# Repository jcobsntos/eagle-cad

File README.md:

# 🦅 EAGLE CAD Projects 

## 🎯 Overview

This repository contains EAGLE CAD design files for various electronics projects, including:

🎨 Footprints, Packages, Devices, and Symbols for PCB design

🛠️ Laboratories covering schematic and board designs

⚡ Multilevel Power Supply Project with a complete schematic and PCB layout

## 🤝 Contributing

Contributions are welcome! 🛠️ Feel free to submit pull requests for improvements, additional laboratories, or new PCB designs.

## Authors

- [@jcobsntos](https://github.com/jcobsntos)

## 🔗 Links

## 🏆 Tools

PCB design software for everyone 🖥️ https://www.autodesk.com/products/eagle/free-download

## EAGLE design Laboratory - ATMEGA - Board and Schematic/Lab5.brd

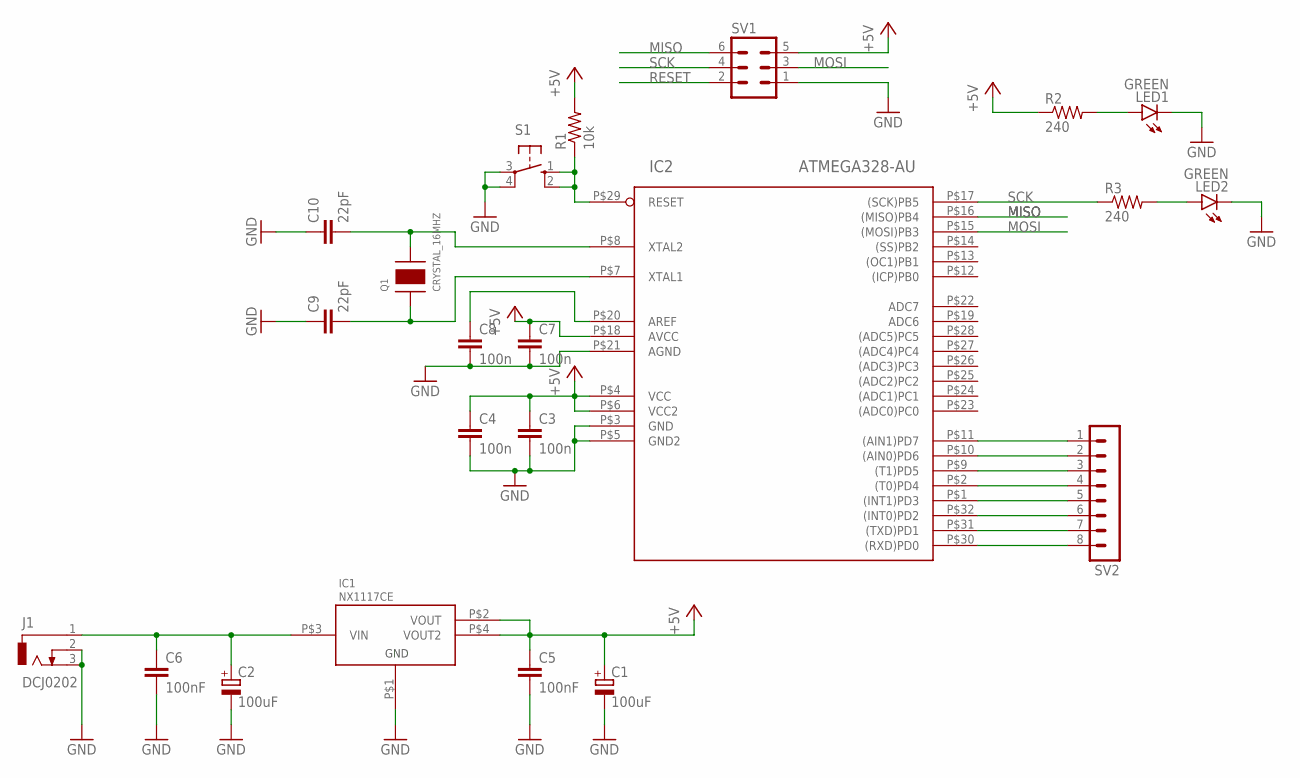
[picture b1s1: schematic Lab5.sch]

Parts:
C1, C2: 100uF; PANASONIC_D
C3, C4, C7, C8: 100n; C0603
C5, C6: 100nF; C0805
C9, C10: 22pF; C0603
IC1: NX1117CE; SOT223_NX
IC2: ATMEGA328-AU; 32-TQFP
J1: DCJ0202
LED1, LED2: GREEN; CHIP-LED0603
Q1: CRYSTAL_16MHZ
R1: 10k; R0603
R2, R3: 240; R0603
S1: 10-XX; B3F-10XX
SV1: MA03-2
SV2: MA08-1

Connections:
+5V: C1.+, C3.1, C4.1, C5.1, C7.1, IC1.P$2 (VOUT), IC1.P$4 (VOUT2), IC2.P$4 (VCC), IC2.P$6 (VCC2), IC2.P$18 (AVCC), R1.2, R2.1, SV1.5
GND: C1.-, C2.-, C3.2, C4.2, C5.2, C6.2, C7.2, C8.2, C9.1, C10.1, IC1.P$1 (GND), IC2.P$3 (GND), IC2.P$5 (GND2), IC2.P$21 (AGND), J1.2, J1.3, LED1.C, LED2.C, S1.3, S1.4 (P1), SV1.1
MISO: IC2.P$16 ((MISO)PB4), SV1.6
MOSI: IC2.P$15 ((MOSI)PB3), SV1.3
unnamed: C2.+, C6.1, IC1.P$3 (VIN), J1.1
unnamed: C8.1, IC2.P$20 (AREF)
unnamed: C9.2, IC2.P$7 (XTAL1), Q1.P$1
unnamed: C10.2, IC2.P$8 (XTAL2), Q1.P$2
unnamed: IC2.P$29 (RESET), R1.1, S1.1 (S), S1.2 (S1)
unnamed: LED1.A, R2.2
unnamed: LED2.A, R3.2
unnamed: IC2.P$11 ((AIN1)PD7), SV2.1
unnamed: IC2.P$10 ((AIN0)PD6), SV2.2
unnamed: IC2.P$9 ((T1)PD5), SV2.3
unnamed: IC2.P$2 ((T0)PD4), SV2.4
unnamed: IC2.P$1 ((INT1)PD3), SV2.5
unnamed: IC2.P$32 ((INT0)PD2), SV2.6
unnamed: IC2.P$31 ((TXD)PD1), SV2.7
unnamed: IC2.P$30 ((RXD)PD0), SV2.8
RESET: SV1.2
SCK: IC2.P$17 ((SCK)PB5), R3.1, SV1.4

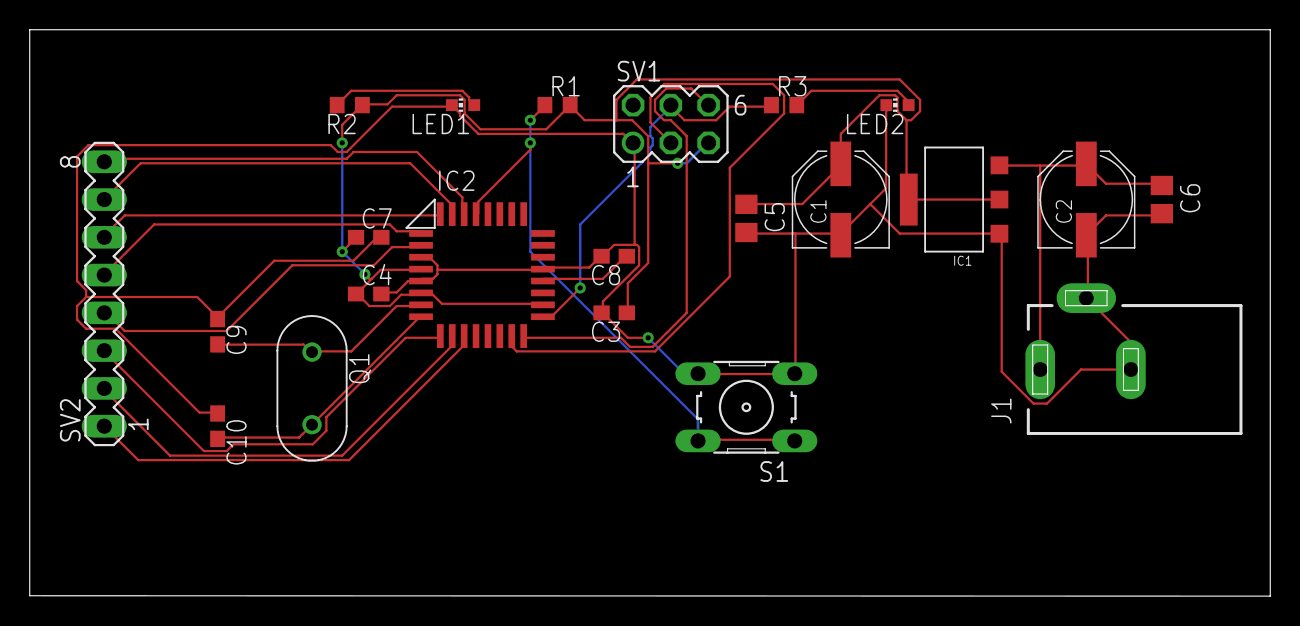
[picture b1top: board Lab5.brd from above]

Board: 2 copper layers, 83.4 x 38.1 mm, 22 parts (0 on the bottom side), 20 nets.

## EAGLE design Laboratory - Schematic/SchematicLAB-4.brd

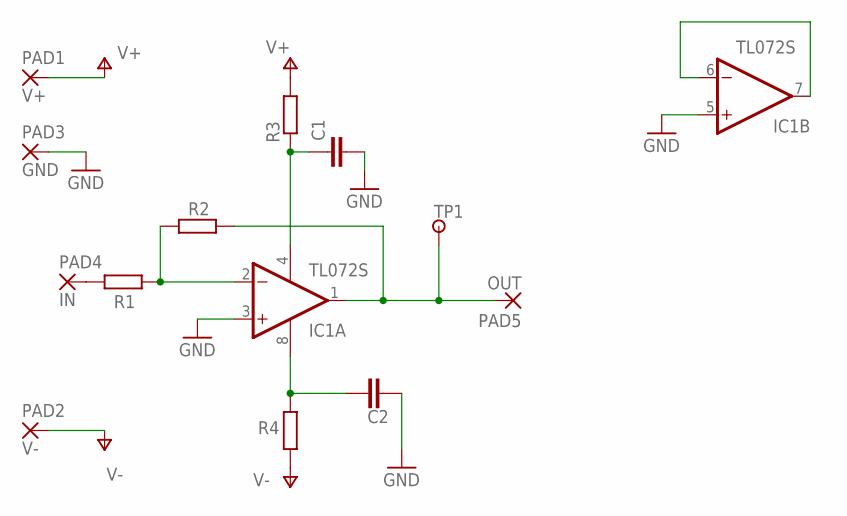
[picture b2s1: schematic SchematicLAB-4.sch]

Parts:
C1, C2: C2.5P; C025-030X050
IC1: TL072S; SOCKED-08
PAD1: V+; 2,54/1,1
PAD2: V-; 2,54/1,1
PAD3: GND; 2,54/1,1
PAD4: IN; 2,54/1,1
PAD5: OUT; 2,54/1,1
R1, R2, R3, R4: R; 0207/10
TP1: PAD-TESTPOINT; 1,6/0,8

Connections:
GND: C1.2, C2.1, IC1.3 (+IN), IC1.5 (+IN), PAD3.1
unnamed: PAD4.1, R1.1
unnamed: IC1.2 (-IN), R1.2, R2.1
unnamed: C1.1, IC1.4 (V-), R3.1
unnamed: IC1.1 (OUT), PAD5.1, R2.2, TP1.1
unnamed: C2.2, IC1.8 (V+), R4.2
unnamed: IC1.6 (-IN), IC1.7 (OUT)
V+: PAD1.1, R3.2
V-: PAD2.1, R4.1

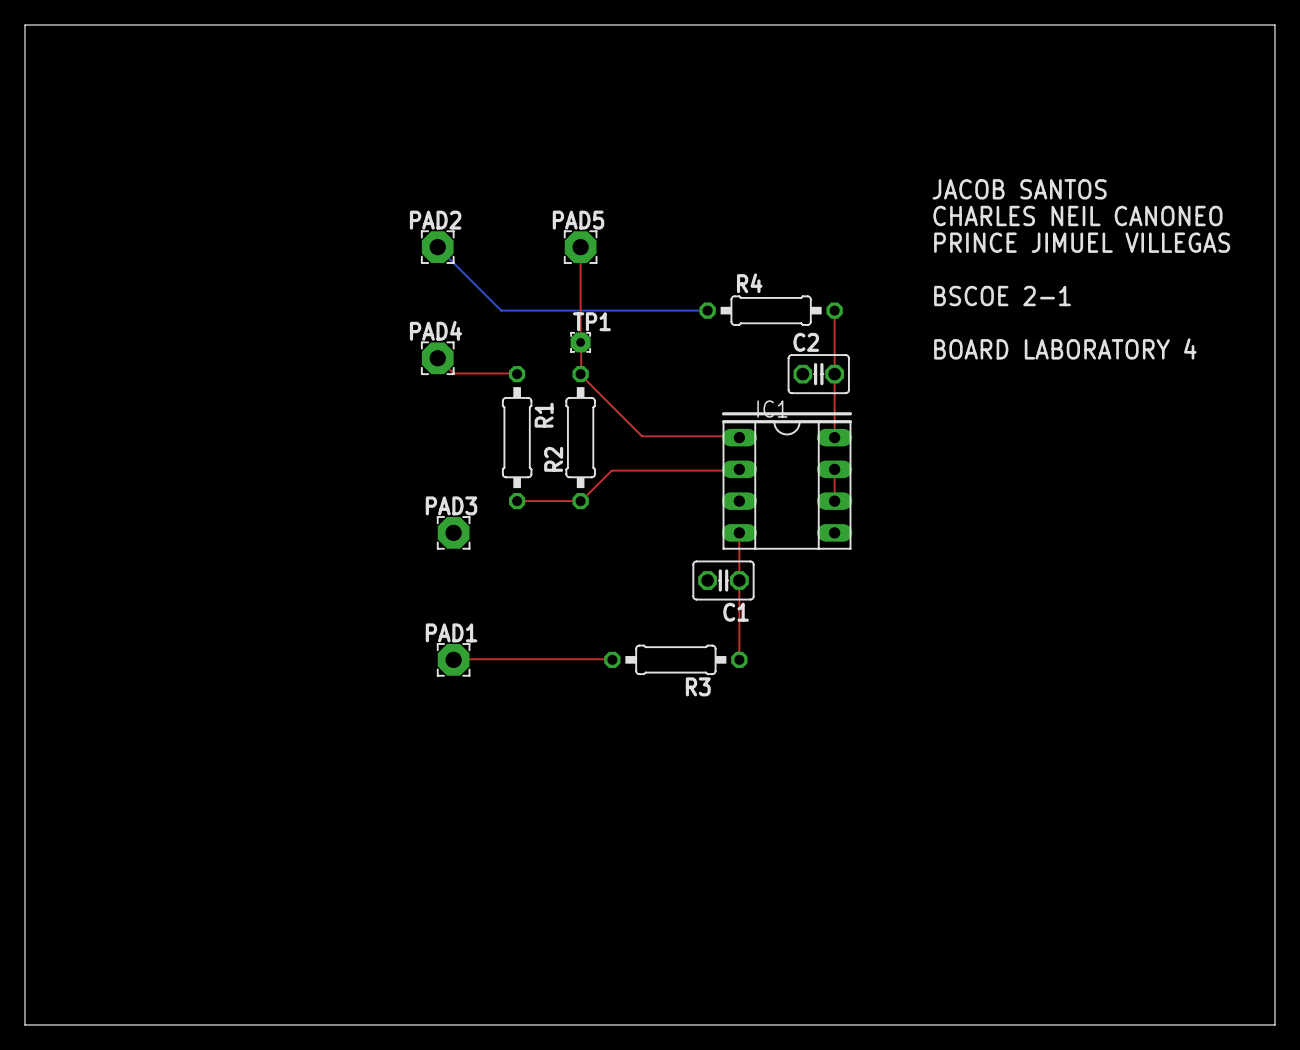
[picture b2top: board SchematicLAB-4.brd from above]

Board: 2 copper layers, 100.0 x 80.0 mm, 13 parts (0 on the bottom side), 9 nets.

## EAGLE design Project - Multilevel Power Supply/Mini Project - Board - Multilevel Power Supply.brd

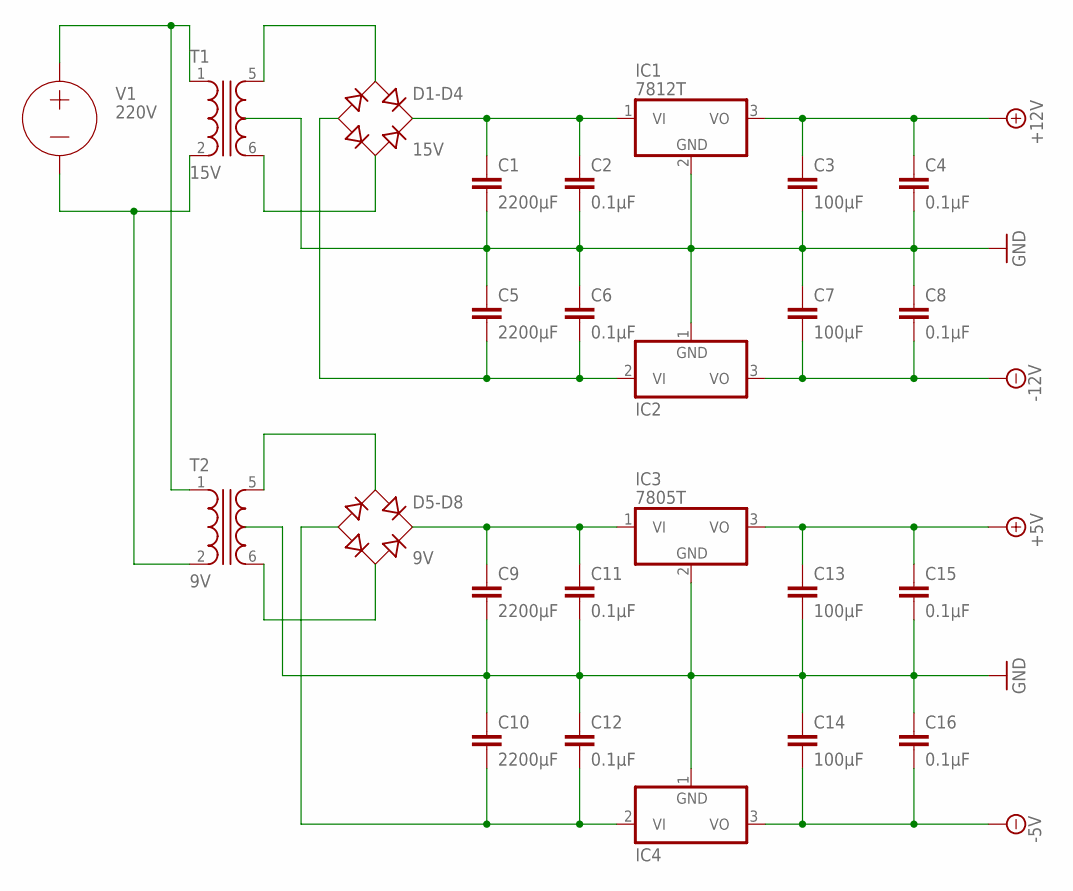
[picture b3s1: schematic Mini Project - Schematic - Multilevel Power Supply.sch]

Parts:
C1, C5, C9, C10: 2200μF; C025-024X044
C2, C4, C6, C8, C11, C12, C15, C16: 0.1μF; C025-024X044
C3, C7, C13, C14: 100μF; C025-024X044
D1-D4: 15V; SOIC-4
D5-D8: 9V; SOIC-4
IC1: 7812T; TO220H
IC2: 7912T; TO220H
IC3: 7805T; TO220H
IC4: 7905T; TO220H
T1: 15V; T70-E
T2: 9V; T70-E

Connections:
+5V: C13.1, C15.1, IC3.3 (VO)
+12V: C3.1, C4.1, IC1.3 (VO)
-5V: C14.2, C16.2, IC4.3 (VO)
-12V: C7.2, C8.2, IC2.3 (VO)
GND: C1.2, C2.2, C3.2, C4.2, C5.1, C6.1, C7.1, C8.1, C9.2, C10.1, C11.2, C12.1, C13.2, C14.1, C15.2, C16.1, IC1.2 (GND), IC2.1 (GND), IC3.2 (GND), IC4.1 (GND)
unnamed: T1.1, T2.1
unnamed: T1.2, T2.2
unnamed: D1-D4.~1 (AC1), T1.5 (S1)
unnamed: D1-D4.~2 (AC2), T1.6 (S2)
unnamed: C1.1, C2.1, D1-D4.+, IC1.1 (VI)
unnamed: C5.2, C6.2, D1-D4.-, IC2.2 (VI)
unnamed: D5-D8.~1 (AC1), T2.5 (S1)
unnamed: D5-D8.~2 (AC2), T2.6 (S2)
unnamed: C9.1, C11.1, D5-D8.+, IC3.1 (VI)
unnamed: C10.2, C12.2, D5-D8.-, IC4.2 (VI)

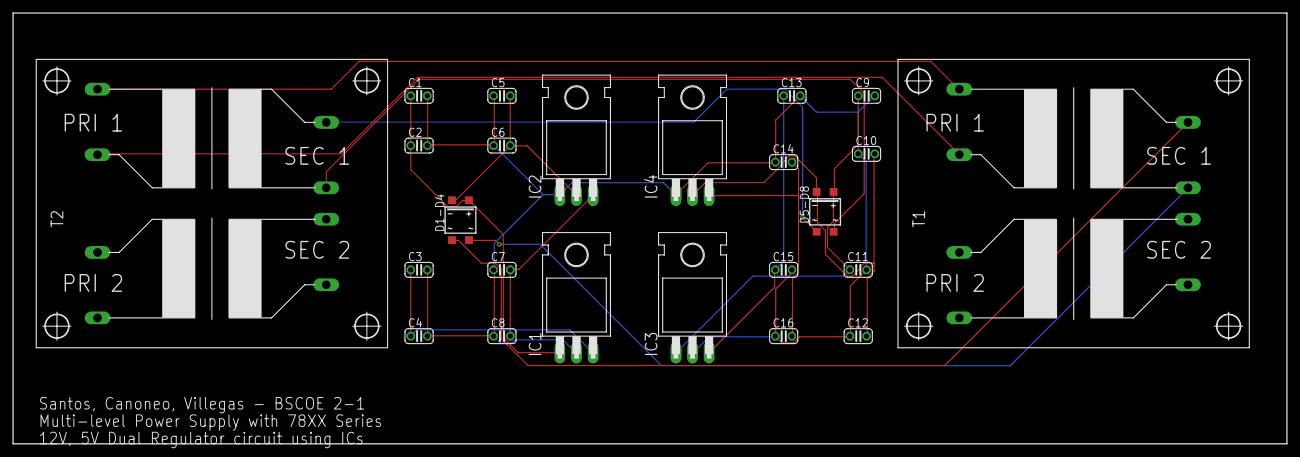
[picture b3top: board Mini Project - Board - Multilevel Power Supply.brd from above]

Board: 2 copper layers, 195.2 x 66.0 mm, 24 parts (0 on the bottom side), 15 nets.

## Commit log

2025-02-24 Create temp
